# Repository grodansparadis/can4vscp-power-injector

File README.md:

# Power injector module for CAN4VSCP

# Abstract

With the power injector you can power the CAN4VSCP bus and also power up to 16 CAN4VSCP modules using the inter module connector. This is a perfect companion board to use when you need to connect a number of CAN4VSCP boards in a cabinet and then connect them to the world.

It have two 120 ohm terminations that can be activated if needed and two RJ-45 connectors for easy connection.

The module has a resettable fuse that allow a maximum of 500 mA for all modules connected to the board. The fuse will trip at about 800 mA. This can be a good safety precaution for wired networks. 

There is also two smaller versions available.

<hr>

This project is part of the <a href="http://www.vscp.org">VSCP (Very Simple Control Protocol) project</a>. 

<hr>

## Project files

### User manual
  * [User Manual](https://grodansparadis.github.io/can4vscp-power-injector/#)

### Schematic, PCB, 3D files etc
  * [Schematics reversion C](./docs/images/power_injector_rev_c.svg)
 * Hardware design files is made in [KiCad](https://kicad.org) and can be found in the `kicad` directory. Valid from reversion C of the hardware.
   * Gerber files for PCB production can be found in the `gerber` directory (in the `kicad` folder).
 * Eagle schema and board files for reversion A, B and C can be found in the `eagle` directory. They are no longer actively updated.

 ### Firmware

 The firmware is developed in [MPLAB X IDE](https://www.microchip.com/mplab/mplab-x-ide) using the [XC8 compiler](https://www.microchip.com/mplab/compilers).

  * Binary release files is available [here](https://github.com/grodansparadis/can4vscp-beijing/releases)

### MDF - Module Description File(s)
  * [MDF file version: 9 Release date: 2020-05-14](http://www.eurosource.se/beijing_2.xml)
  * [MDF file version: 1.0.0 Release date: 2015-06-15](http://www.eurosource.se/beijing_1.xml)

### Support
If you need support, please open an issue in the [GitHub repository](https://github.com/grodansparadis/can4vscp-beijing/issues).

### Buy a ready made modules
You can buy a ready made module from [Grodans Paradis](http://www.grodansparadis.com).

### Project related links
  * [VSCP project](https://www.vscp.org)
  * [VSCP Documentation site](https://docs.vscp.org/)
  * [VSCP Wiki](https://github.com/grodansparadis/vscp/wiki)

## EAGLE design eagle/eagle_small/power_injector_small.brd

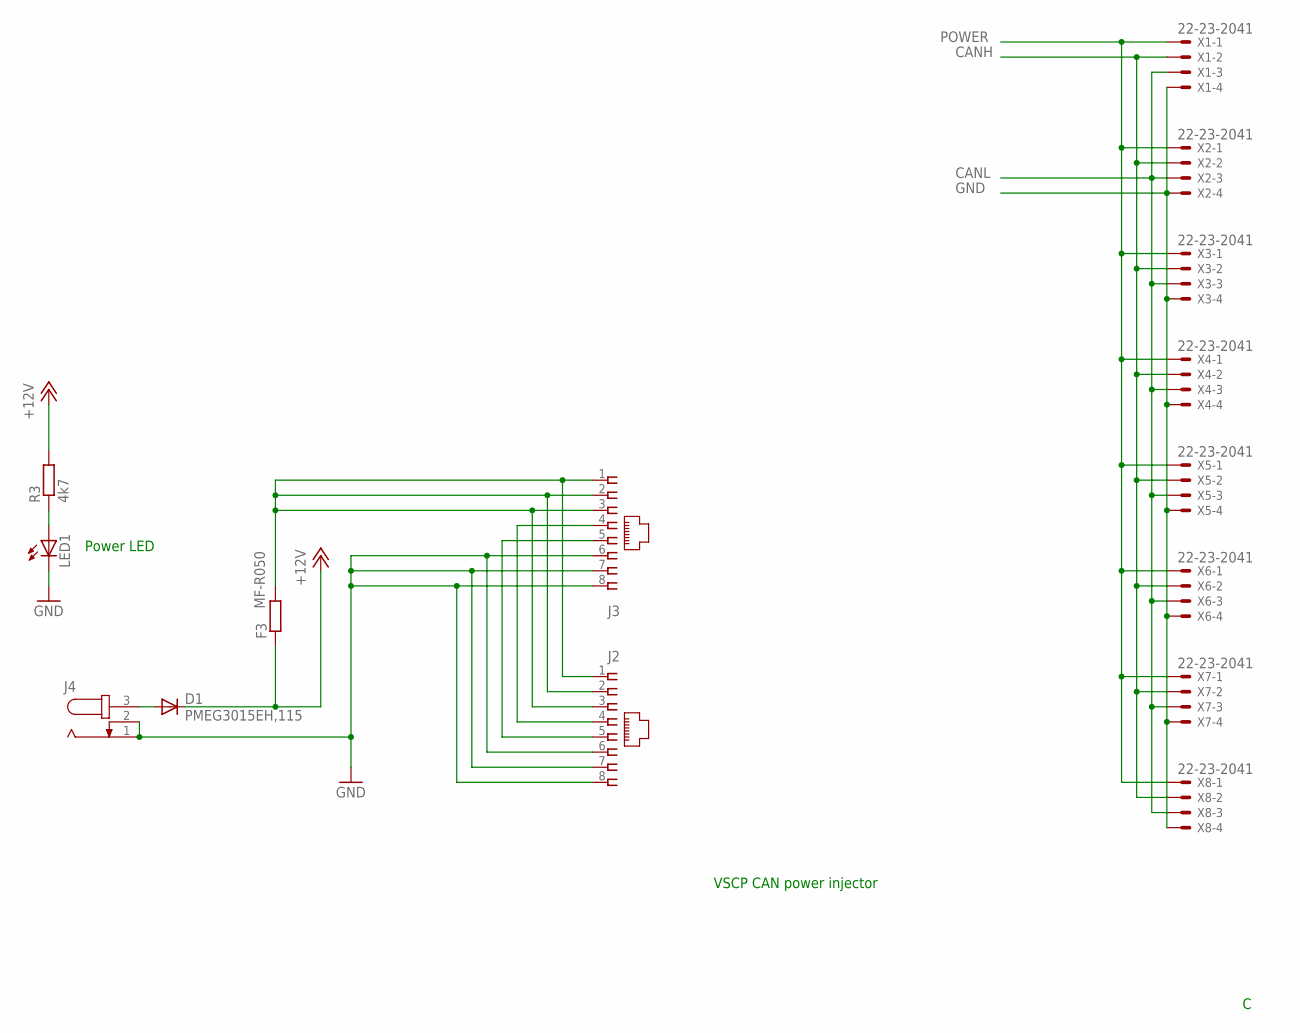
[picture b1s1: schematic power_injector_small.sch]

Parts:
D1: PMEG3015EH,115; SMB
F3: MF-R050; 0204/5
J2, J3: A00-108-220-450; RJ-45
J4: JACK-PLUG0; SPC4077
LED1: LEDCHIP-LED0805; CHIP-LED0805
R3: 4k7; R0805
X1, X2, X3, X4, X5, X6, X7, X8: 22-23-2041

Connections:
+12V: D1.C, F3.1, R3.2
CANH: J2.4, J3.4, X1.2, X2.2, X3.2, X4.2, X5.2, X6.2, X7.2, X8.2
CANL: J2.5, J3.5, X1.3, X2.3, X3.3, X4.3, X5.3, X6.3, X7.3, X8.3
GND: J2.6, J2.7, J2.8, J3.6, J3.7, J3.8, J4.1, J4.2, LED1.C, X1.4, X2.4, X3.4, X4.4, X5.4, X6.4, X7.4, X8.4
unnamed: LED1.A, R3.1
unnamed: D1.A, J4.3
POWER: F3.2, J2.1, J2.2, J2.3, J3.1, J3.2, J3.3, X1.1, X2.1, X3.1, X4.1, X5.1, X6.1, X7.1, X8.1

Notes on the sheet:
Power LED
VSCP CAN power injector

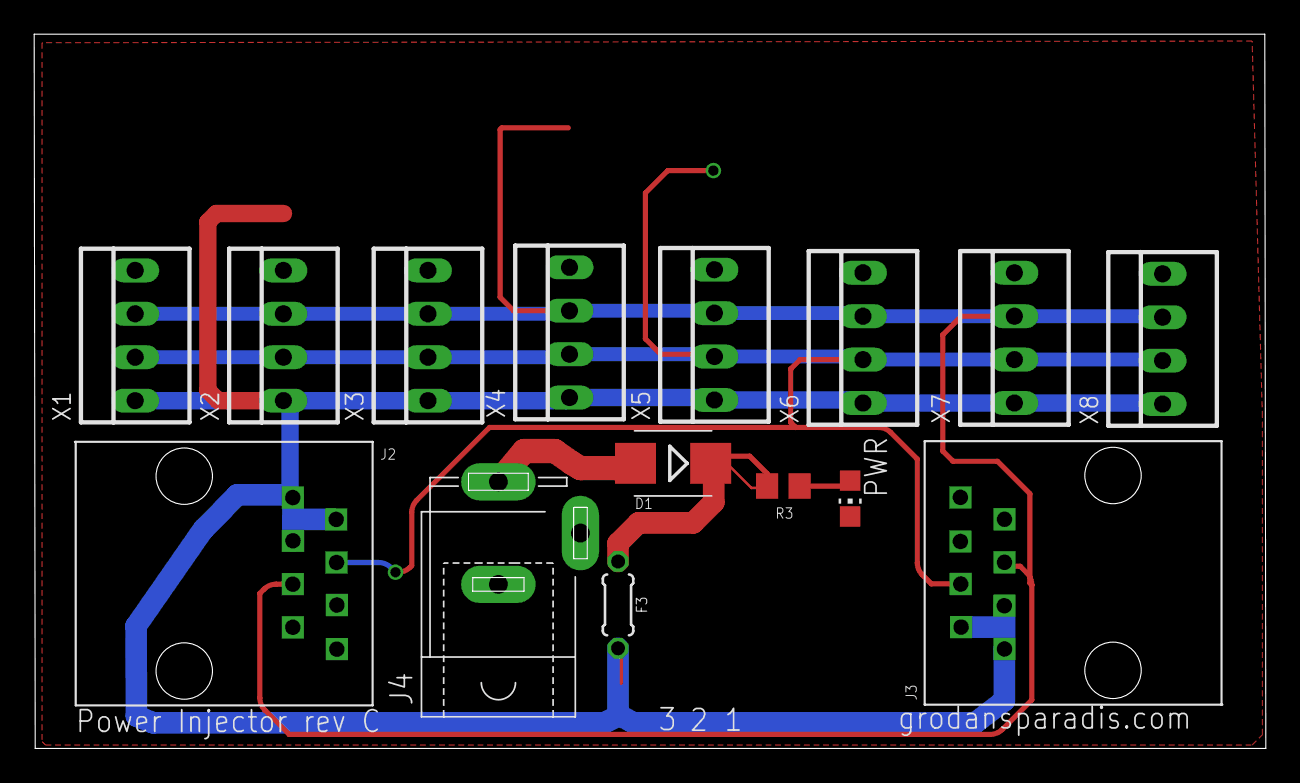
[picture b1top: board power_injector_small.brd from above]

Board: 2 copper layers, 72.1 x 41.8 mm, 15 parts (0 on the bottom side), 7 nets.

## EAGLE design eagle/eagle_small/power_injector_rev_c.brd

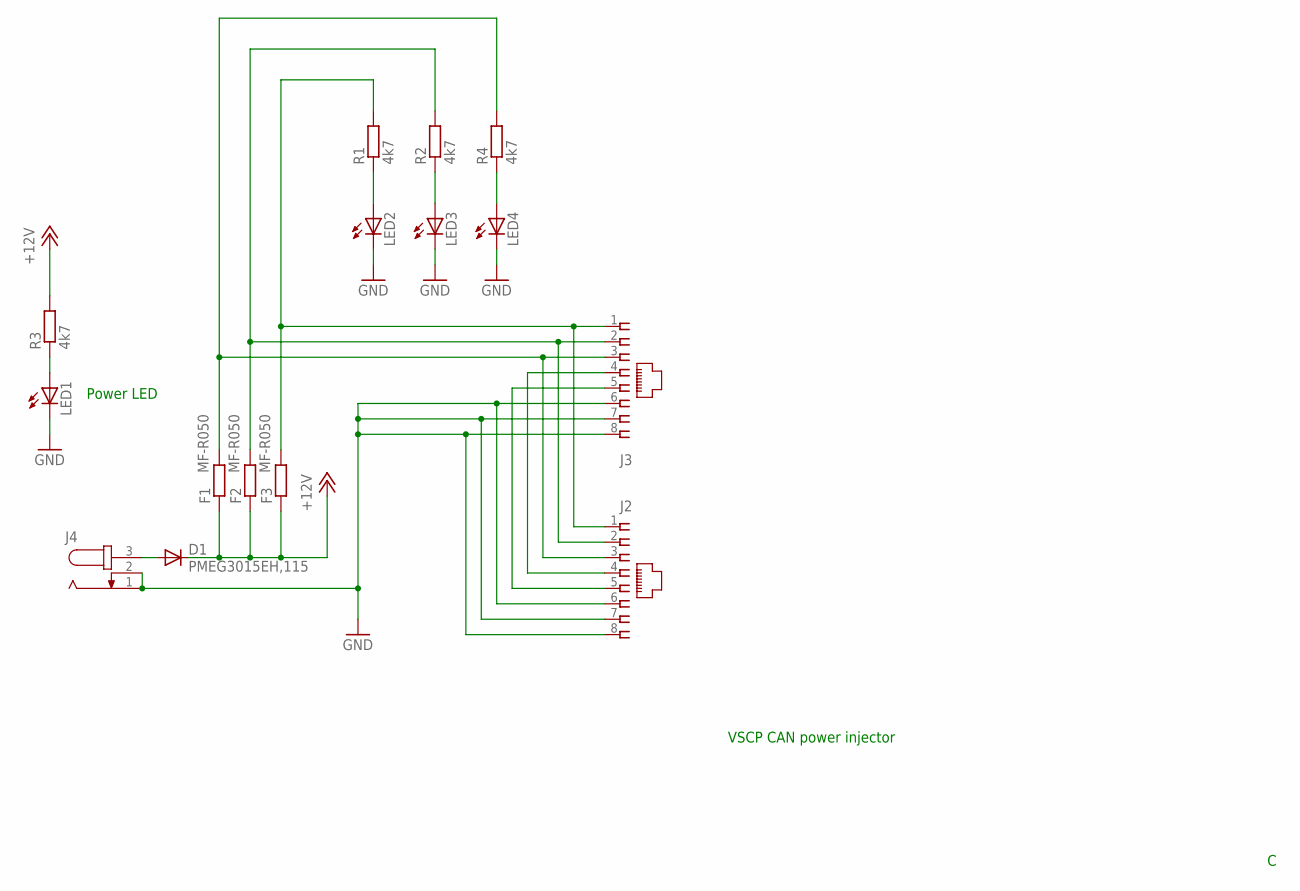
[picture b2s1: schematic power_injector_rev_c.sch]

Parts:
D1: PMEG3015EH,115; SMB
F1, F2, F3: MF-R050; 0204/5
J2, J3: A00-108-220-450; RJ-45
J4: JACK-PLUG0; SPC4077
LED1, LED2, LED3, LED4: LEDCHIP-LED0805; CHIP-LED0805
R1, R2, R3, R4: 4k7; R0805

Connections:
+12V: D1.C, F1.1, F2.1, F3.1, R3.2
GND: J2.6, J2.7, J2.8, J3.6, J3.7, J3.8, J4.1, J4.2, LED1.C, LED2.C, LED3.C, LED4.C
unnamed: LED3.A, R2.1
unnamed: LED1.A, R3.1
unnamed: J2.4, J3.4
unnamed: J2.5, J3.5
unnamed: LED4.A, R4.1
unnamed: LED2.A, R1.1
unnamed: D1.A, J4.3
PWR1: F3.2, J2.1, J3.1, R1.2
PWR2: F2.2, J2.2, J3.2, R2.2
PWR3: F1.2, J2.3, J3.3, R4.2

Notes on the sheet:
Power LED
VSCP CAN power injector

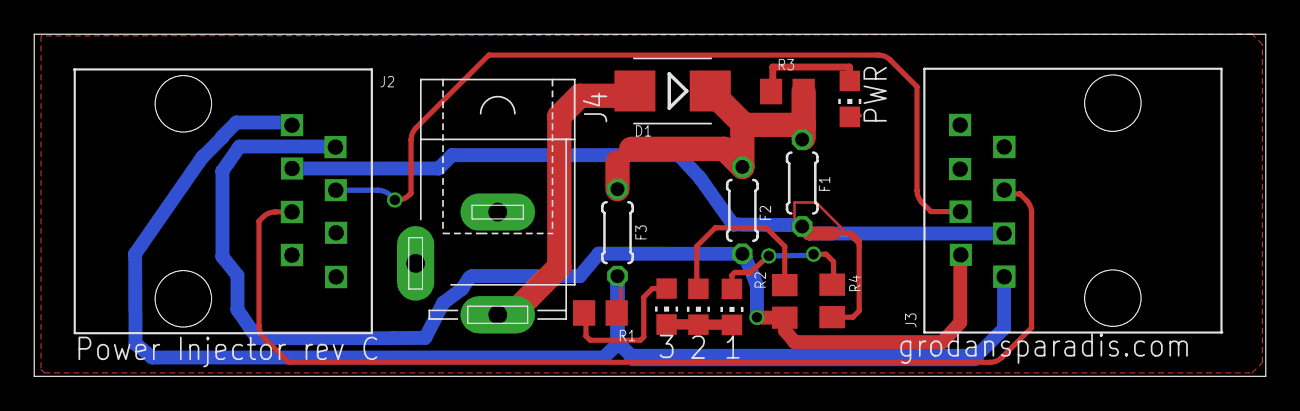
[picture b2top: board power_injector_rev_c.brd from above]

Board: 2 copper layers, 72.0 x 20.0 mm, 15 parts (0 on the bottom side), 12 nets.

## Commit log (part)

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2025-08-18 Convert schema to kicad
2025-09-30 Changed license to MIT
2025-10-01 Rearranged files (in a more logical way)
2025-10-01 Added image files for the module
2025-10-01 Added descriptions of connectors
2025-10-01 Added power jack picture
2026-05-05 Updated license to CERN
2026-05-05 Added screw terminal version
